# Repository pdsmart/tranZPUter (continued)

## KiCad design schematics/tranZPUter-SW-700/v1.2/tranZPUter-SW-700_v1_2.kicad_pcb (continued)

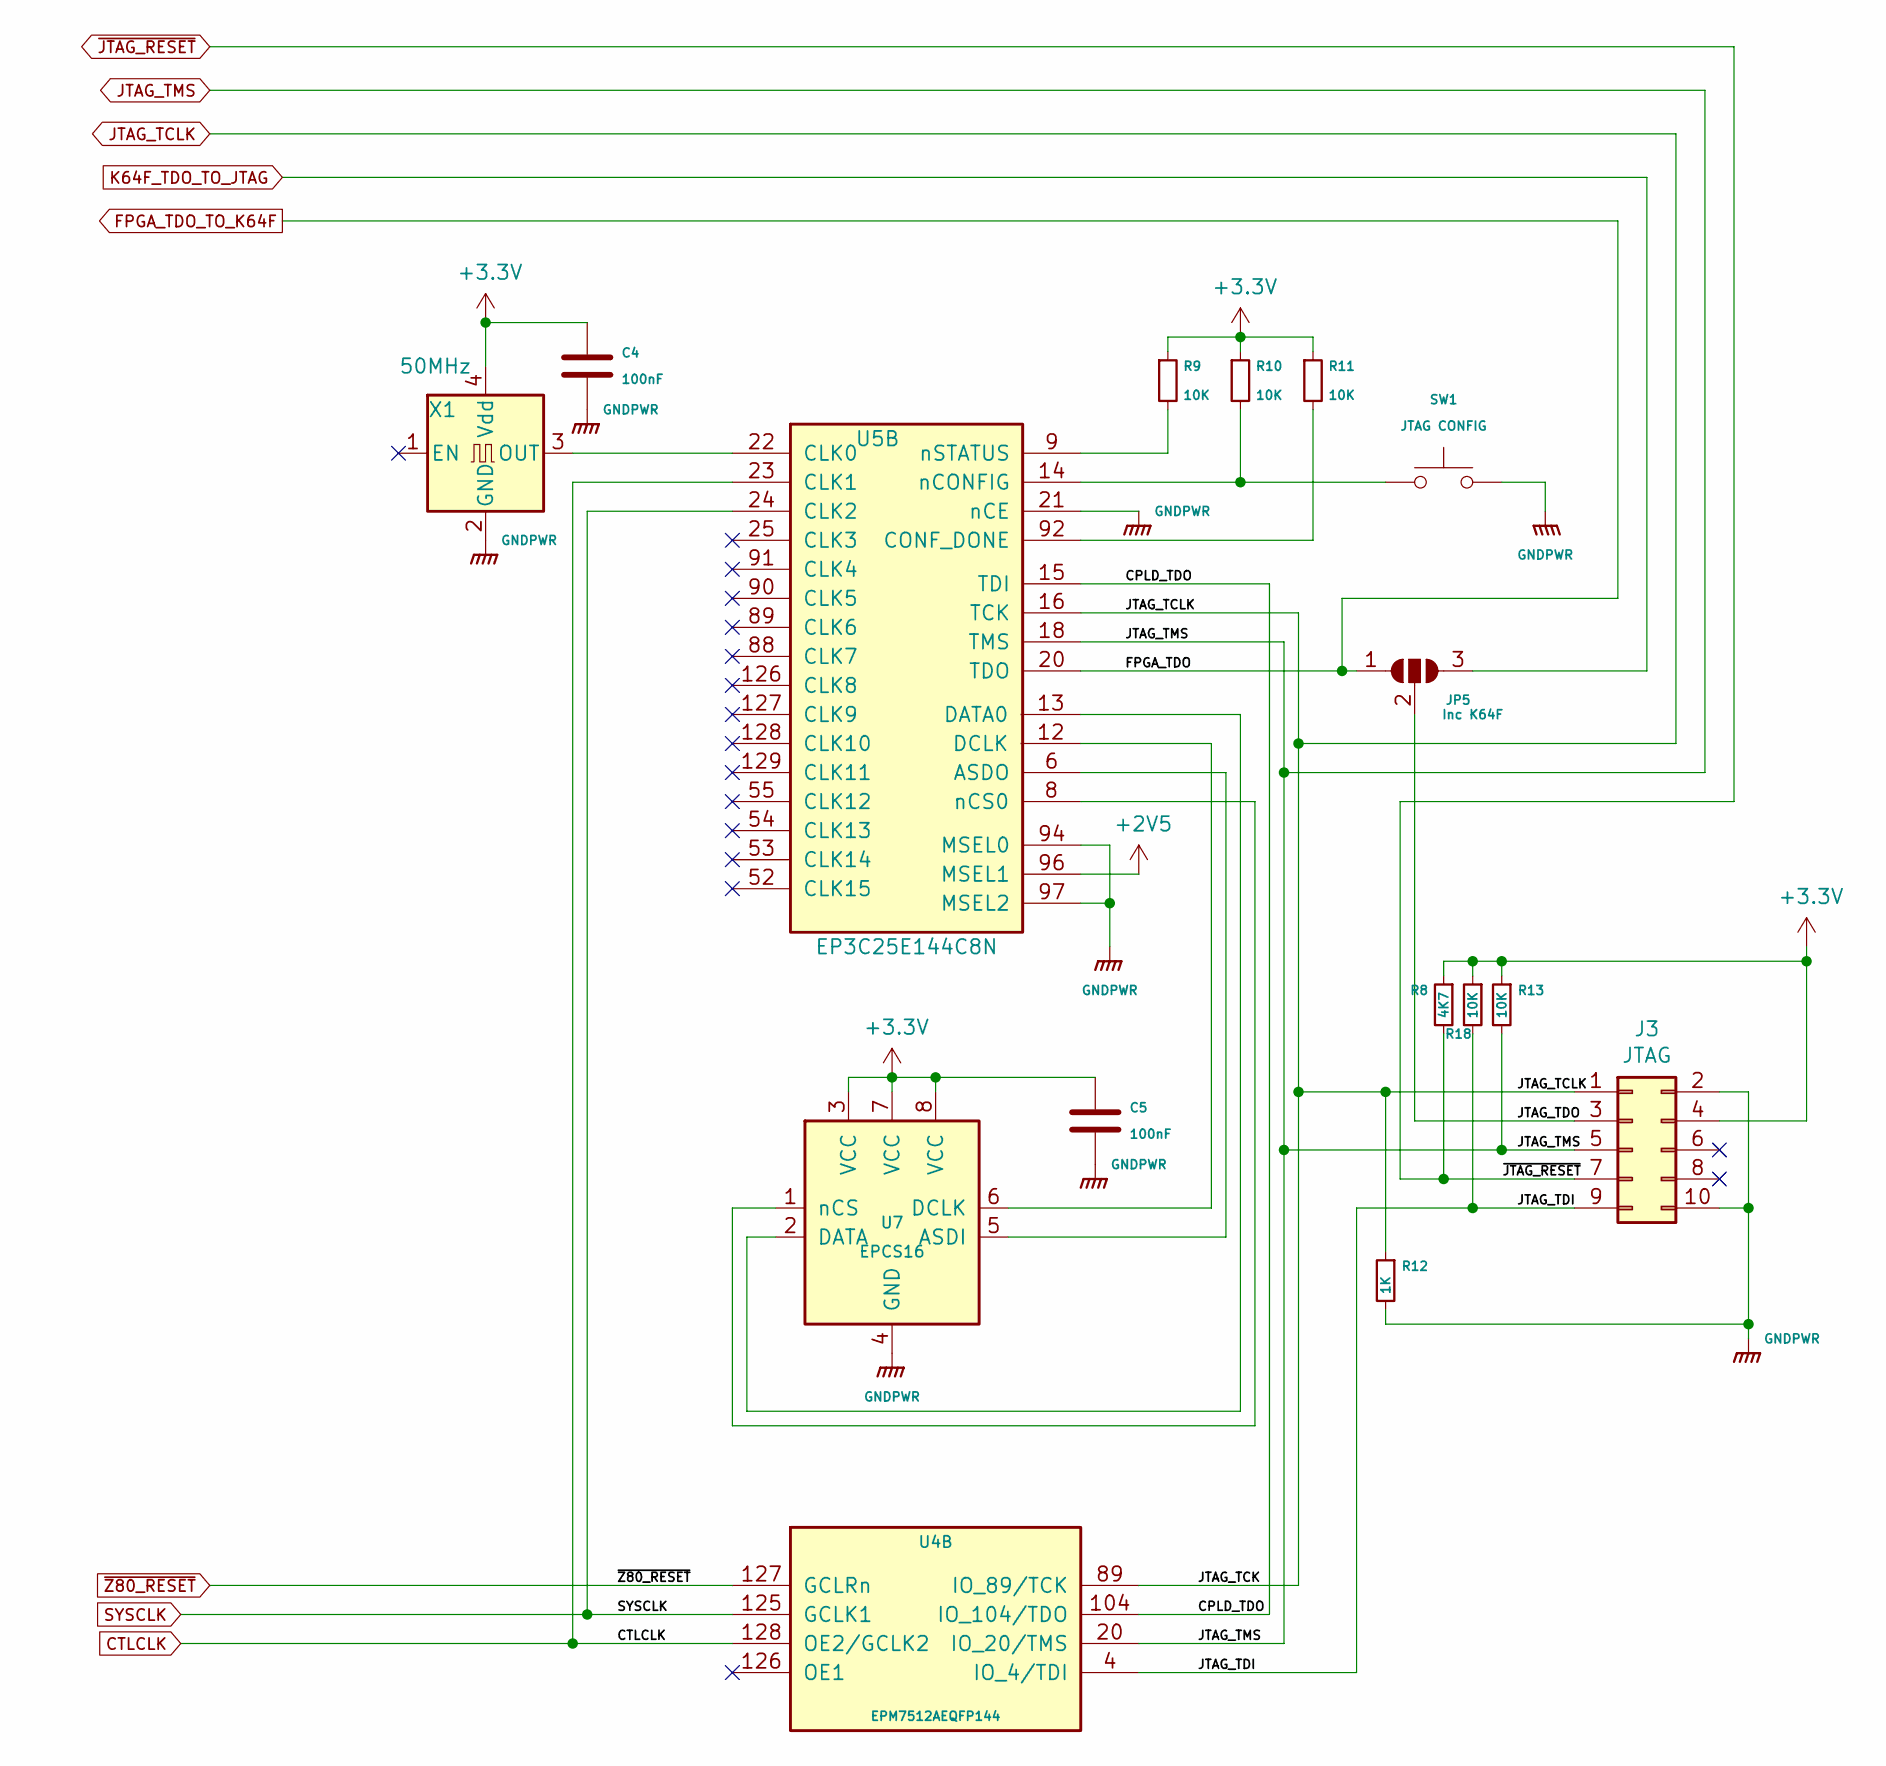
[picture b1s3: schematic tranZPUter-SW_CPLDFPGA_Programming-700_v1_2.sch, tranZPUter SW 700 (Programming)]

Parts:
C4, C5: 100nF; C_0603_1608Metric_Pad1.05x0.95mm_HandSolder
J3: JTAG; PinHeader_2x05_P2.54mm_Horizontal_NoBug
JP5: Inc K64F; SolderJumper-3_Open
R8: 4K7; R_0805_2012Metric_Pad1.15x1.40mm_HandSolder
R9, R10, R11, R13, R18: 10K; R_0805_2012Metric_Pad1.15x1.40mm_HandSolder
R12: 1K; R_0805_2012Metric_Pad1.15x1.40mm_HandSolder
SW1: JTAG CONFIG; SW_SPST_B3S-1000
U4: EPM7512AEQFP144; TQFP-144_20x20mm_P0.5mm
U5: EP3C25E144C8N; EQFP-144-1EP_20x20mm_P0.5mm_EP6.61x5.615mm
U7: EPCS16; SOIC-8_3.9x4.9mm_P1.27mm
X1: 50MHz; Oscillator_SMD_Abracon_ASE-4Pin_3.2x2.5mm

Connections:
+2V5: U5.96 (MSEL1); also elsewhere on the board
/CPLD and FPGA Programming/CPLD_TDO: U4.104 (IO_104/TDO), U5.15 (TDI)
/CPLD and FPGA Programming/JTAG_TDI: J3.9, R18.2, U4.4 (IO_4/TDI)
/CPLD and FPGA Programming/JTAG_TDO: J3.3, JP5.2 (C)
CTLCLK: U4.128 (OE2/GCLK2), U5.23 (CLK1); also elsewhere on the board
FPGA_TDO_TO_K64F: JP5.1 (A), U5.20 (TDO); also elsewhere on the board
GNDPWR: C4.2, C5.2, J3.2, J3.10, R12.2, SW1.2, U5.21 (nCE), U5.94 (MSEL0), U5.97 (MSEL2), U7.4 (GND), X1.2 (GND); also elsewhere on the board
JTAG_TCLK: J3.1, R12.1, U4.89 (IO_89/TCK), U5.16 (TCK); also elsewhere on the board
JTAG_TMS: J3.5, R13.2, U4.20 (IO_20/TMS), U5.18 (TMS); also elsewhere on the board
K64F_TDO_TO_JTAG: JP5.3 (B); also elsewhere on the board
unnamed: R9.2, U5.9 (nSTATUS)
unnamed: R10.2, SW1.1, U5.14 (nCONFIG)
unnamed: R11.2, U5.92 (CONF_DONE)
unnamed: U5.6 (ASDO), U7.5 (ASDI)
unnamed: U5.8 (nCS0), U7.1 (nCS)
unnamed: U5.12 (DCLK), U7.6 (DCLK)
unnamed: U5.13 (DATA0), U7.2 (DATA)
unnamed: U5.22 (CLK0), X1.3 (OUT)
SYSCLK: U4.125 (GCLK1), U5.24 (CLK2); also elsewhere on the board
~JTAG_RESET~: J3.7, R8.2; also elsewhere on the board
~Z80_RESET~: U4.127 (GCLRn); also elsewhere on the board

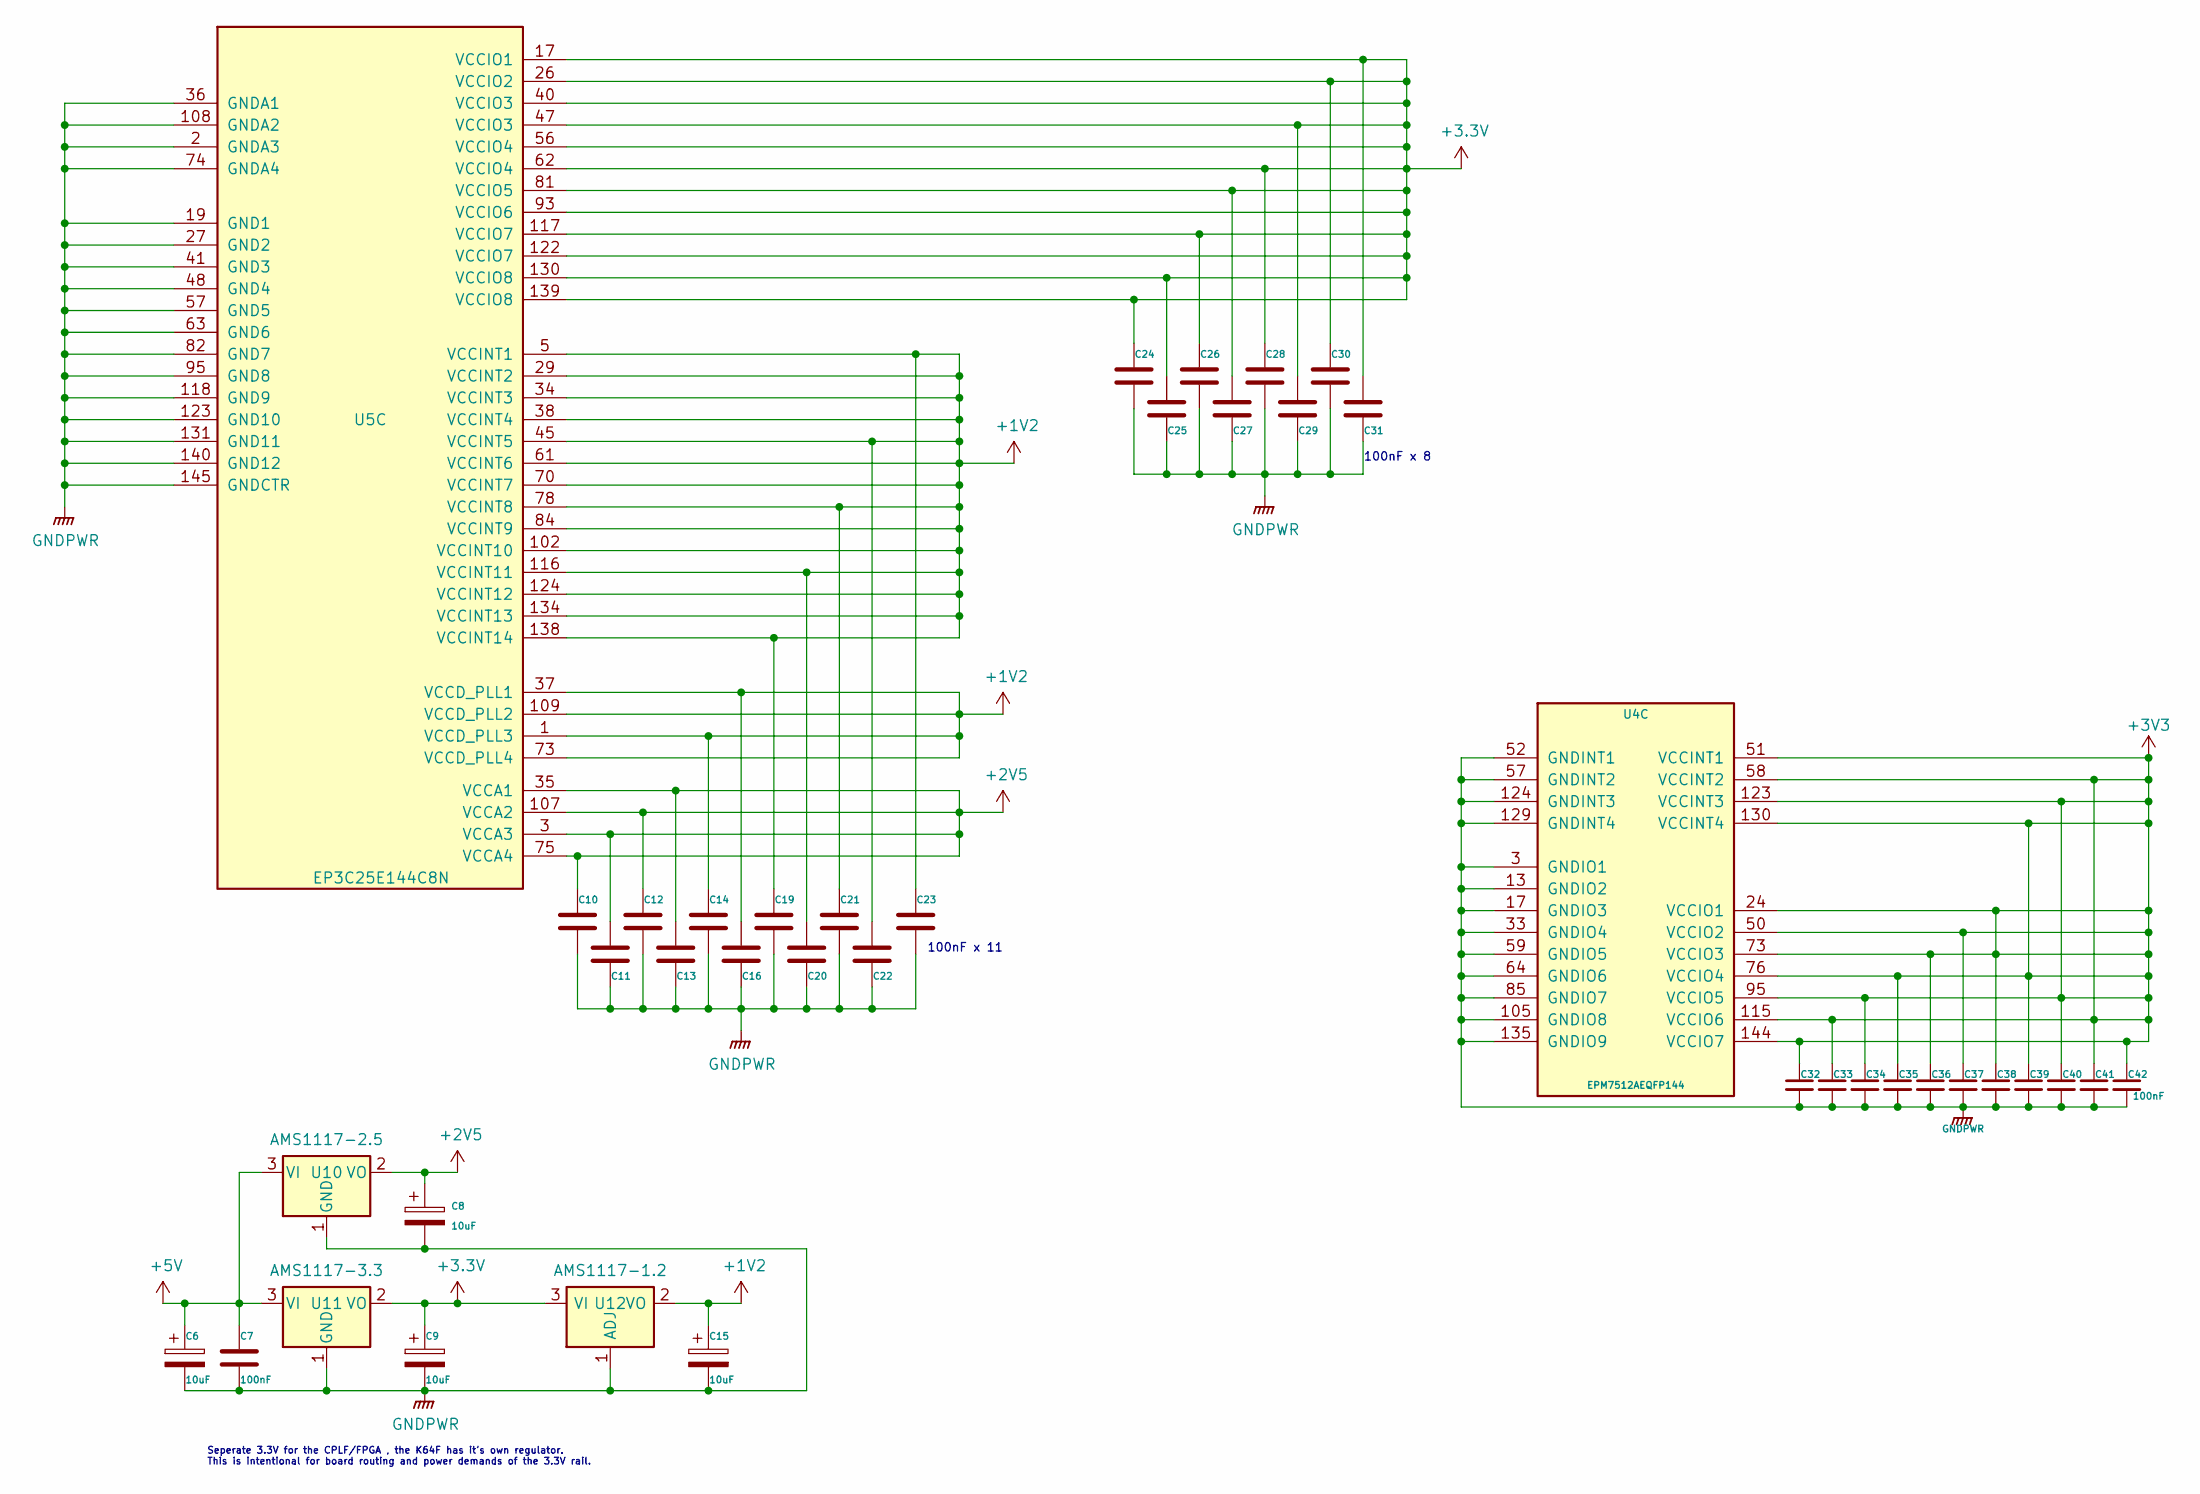
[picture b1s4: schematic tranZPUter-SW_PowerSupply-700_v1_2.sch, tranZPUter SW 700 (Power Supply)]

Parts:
C6, C8, C9, C15: 10uF; C_0603_1608Metric_Pad1.05x0.95mm_HandSolder
C7, C10, C11, C12, C13, C14, C16, C19, C20, C21, C22, C23, C27: 100nF; C_0603_1608Metric_Pad1.05x0.95mm_HandSolder
C24, C25, C26, C28, C29, C30, C31: 100nF; C_0805_2012Metric
C32, C33, C34, C35, C36, C37, C38, C39, C40, C41, C42: 100nF; C_0603_1608Metric
U4: EPM7512AEQFP144; TQFP-144_20x20mm_P0.5mm
U5: EP3C25E144C8N; EQFP-144-1EP_20x20mm_P0.5mm_EP6.61x5.615mm
U10: AMS1117-2.5; SOT-223-3_TabPin2
U11: AMS1117-3.3; SOT-223-3_TabPin2
U12: AMS1117-1.2; SOT-223-3_TabPin2

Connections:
+1V2: C14.1, C15.1, C16.1, C19.1, C20.1, C21.1, C22.1, C23.1, U5.1 (VCCD_PLL3), U5.5 (VCCINT1), U5.29 (VCCINT2), U5.34 (VCCINT3), U5.37 (VCCD_PLL1), U5.38 (VCCINT4), U5.45 (VCCINT5), U5.61 (VCCINT6), U5.70 (VCCINT7), U5.73 (VCCD_PLL4), U5.78 (VCCINT8), U5.84 (VCCINT9), U5.102 (VCCINT10), U5.109 (VCCD_PLL2), U5.116 (VCCINT11), U5.124 (VCCINT12), U5.134 (VCCINT13), U5.138 (VCCINT14), U12.2 (VO)
+2V5: C8.1, C10.1, C11.1, C12.1, C13.1, U5.3 (VCCA3), U5.35 (VCCA1), U5.75 (VCCA4), U5.107 (VCCA2), U10.2 (VO); also elsewhere on the board
+5V: C6.1, C7.1, U10.3 (VI), U11.3 (VI); also elsewhere on the board
GNDPWR: C6.2, C7.2, C8.2, C9.2, C10.2, C11.2, C12.2, C13.2, C14.2, C15.2, C16.2, C19.2, C20.2, C21.2, C22.2, C23.2, C24.2, C25.2, C26.2, C27.2, C28.2, C29.2, C30.2, C31.2, C32.2, C33.2, C34.2, C35.2, C36.2, C37.2, C38.2, C39.2, C40.2, C41.2, C42.2, U4.3 (GNDIO1), U4.13 (GNDIO2), U4.17 (GNDIO3), U4.33 (GNDIO4), U4.52 (GNDINT1), U4.57 (GNDINT2), U4.59 (GNDIO5), U4.64 (GNDIO6), U4.85 (GNDIO7), U4.105 (GNDIO8), U4.124 (GNDINT3), U4.129 (GNDINT4), U4.135 (GNDIO9), U5.2 (GNDA3), U5.19 (GND1), U5.27 (GND2), U5.36 (GNDA1), U5.41 (GND3), U5.48 (GND4), U5.57 (GND5), U5.63 (GND6), U5.74 (GNDA4), U5.82 (GND7), U5.95 (GND8), U5.108 (GNDA2), U5.118 (GND9), U5.123 (GND10), U5.131 (GND11), U5.140 (GND12), U5.145 (GNDCTR), U10.1 (GND), U11.1 (GND), U12.1 (ADJ); also elsewhere on the board

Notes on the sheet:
100nF x 11
100nF x 8
Seperate 3.3V for the CPLF/FPGA , the K64F has it’s own regulator. This is intentional for board routing and power demands of the 3.3V rail.

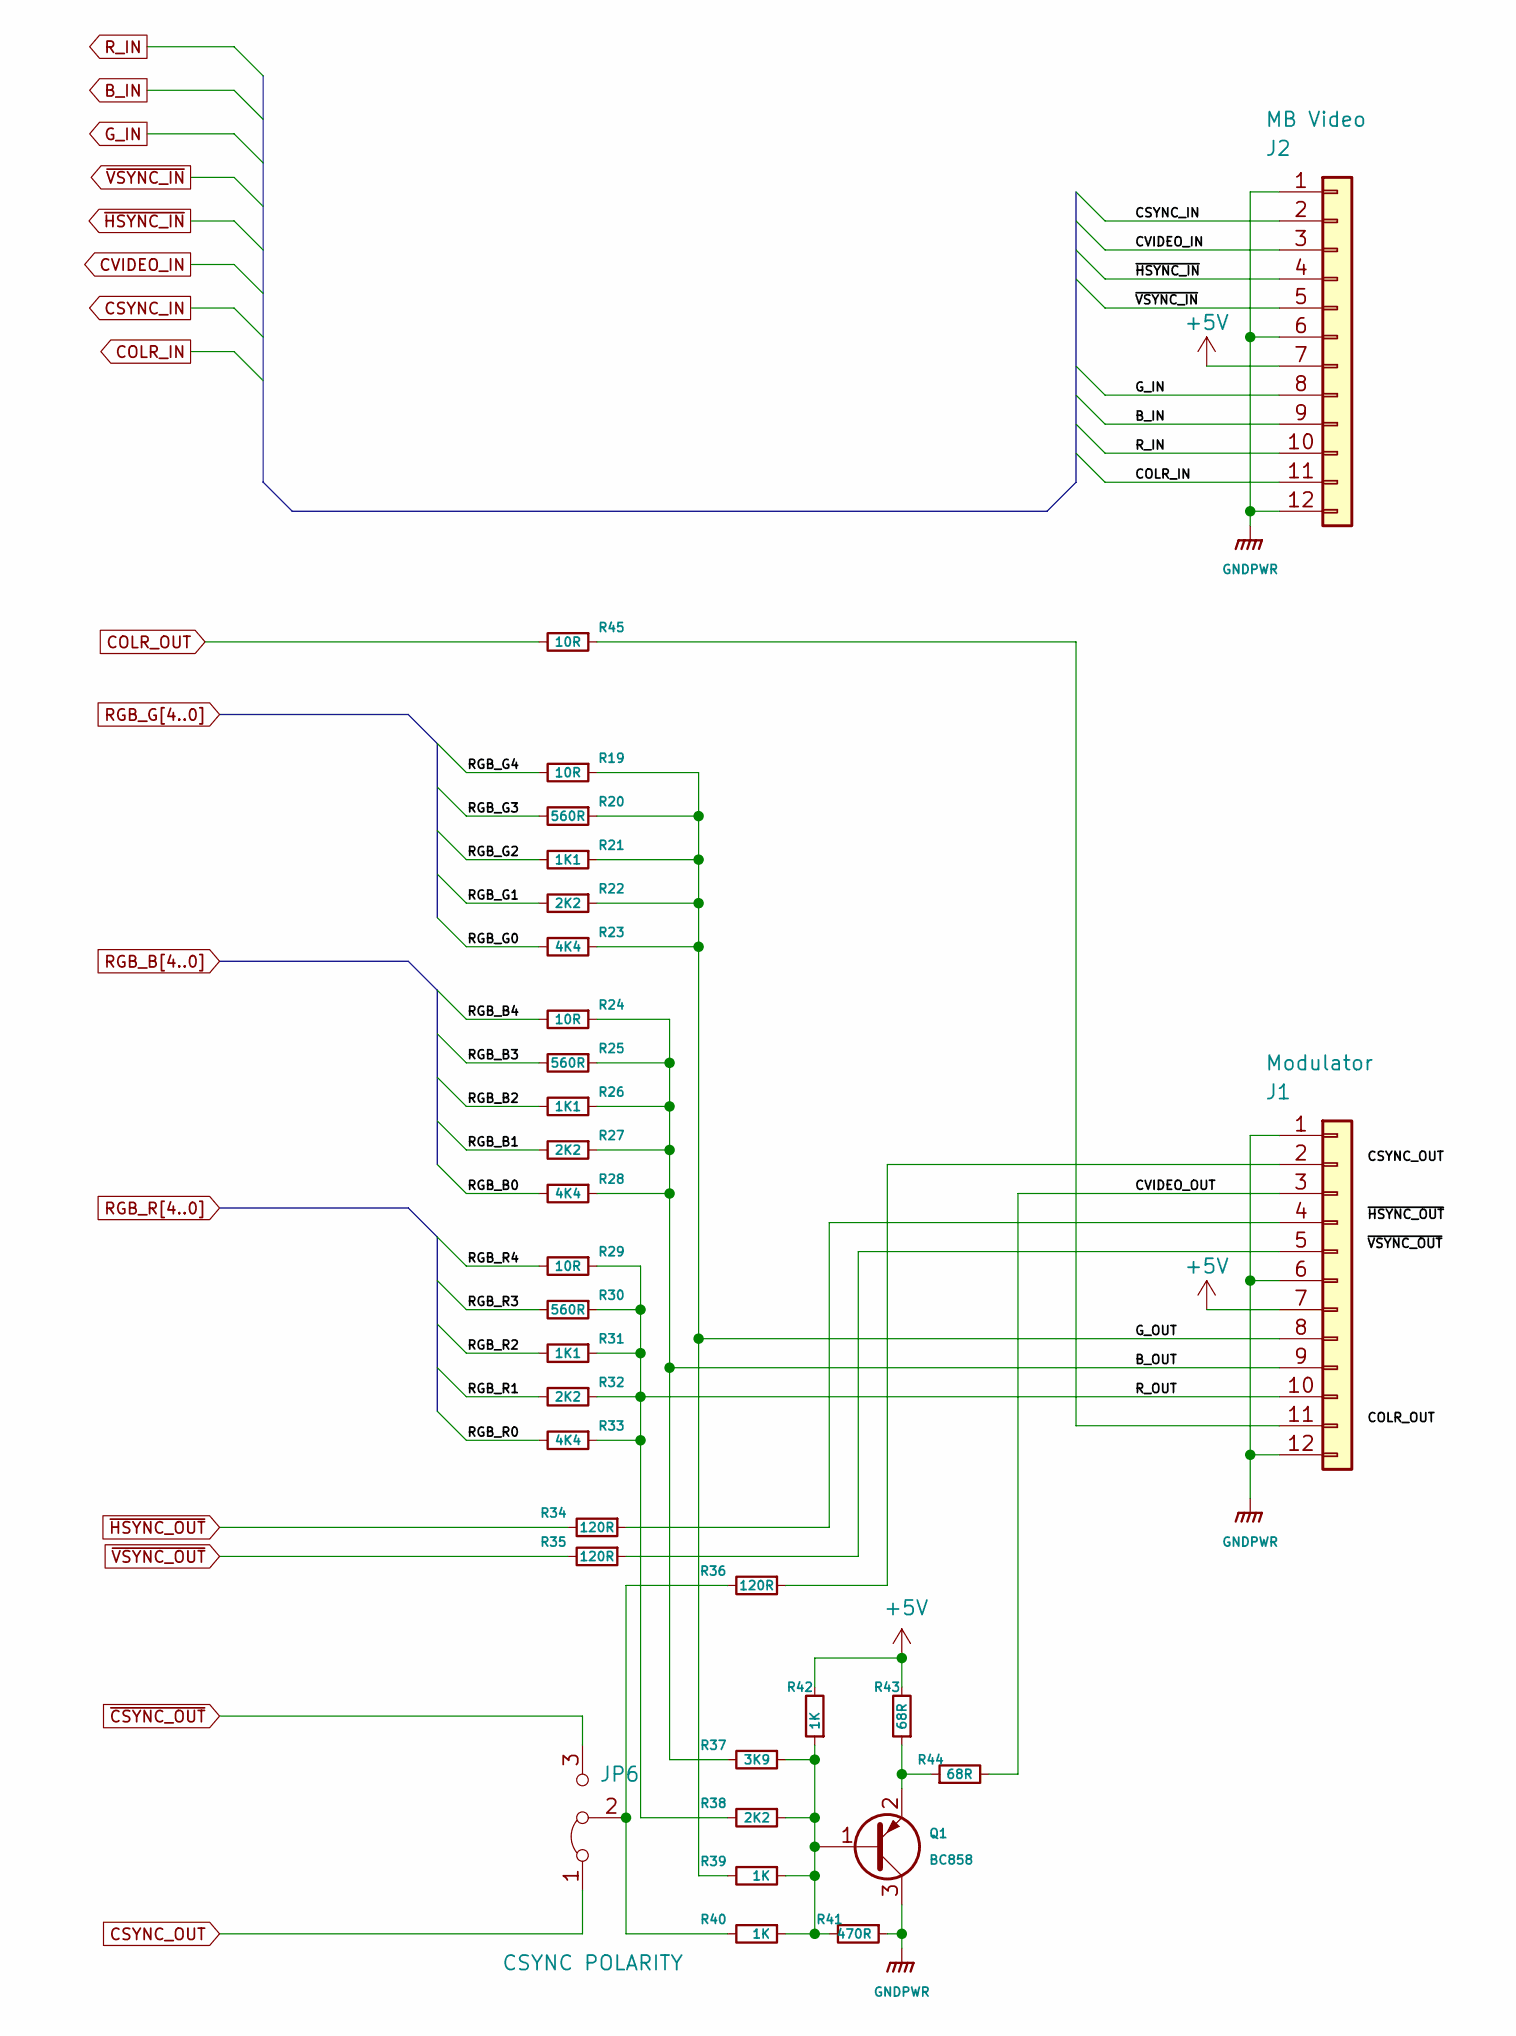
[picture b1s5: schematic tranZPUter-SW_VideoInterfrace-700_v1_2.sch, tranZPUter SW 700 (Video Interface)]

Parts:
J1: Modulator; PinHeader_1x12_P2.54mm_Vertical
J2: MB Video; PinHeader_1x12_P2.54mm_Vertical
JP6: CSYNC POLARITY; PinHeader_1x03_P2.00mm_Vertical
Q1: BC858; SOT-23
R19, R24, R29, R45: 10R; R_0805_2012Metric_Pad1.15x1.40mm_HandSolder
R20, R25, R30: 560R; R_0805_2012Metric_Pad1.15x1.40mm_HandSolder
R21, R26, R31: 1K1; R_0805_2012Metric_Pad1.15x1.40mm_HandSolder
R22, R27, R32, R38: 2K2; R_0805_2012Metric_Pad1.15x1.40mm_HandSolder
R23, R28, R33: 4K4; R_0805_2012Metric_Pad1.15x1.40mm_HandSolder
R34, R35, R36: 120R; R_0805_2012Metric_Pad1.15x1.40mm_HandSolder
R37: 3K9; R_0805_2012Metric_Pad1.15x1.40mm_HandSolder
R39, R40, R42: 1K; R_0805_2012Metric_Pad1.15x1.40mm_HandSolder
R41: 470R; R_0805_2012Metric_Pad1.15x1.40mm_HandSolder
R43, R44: 68R; R_0805_2012Metric_Pad1.15x1.40mm_HandSolder

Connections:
+5V: J1.7, J2.7, R42.2, R43.2; also elsewhere on the board
/Video Interface/B_OUT: J1.9, R24.1, R25.1, R26.1, R27.1, R28.1, R37.2
/Video Interface/CVIDEO_OUT: J1.3, R44.2
/Video Interface/G_OUT: J1.8, R19.1, R20.1, R21.1, R22.1, R23.1, R39.2
/Video Interface/R_OUT: J1.10, R29.1, R30.1, R31.1, R32.1, R33.1, R38.2
B_IN: J2.9; also elsewhere on the board
COLR_IN: J2.11; also elsewhere on the board
COLR_OUT: R45.2; also elsewhere on the board
CSYNC_IN: J2.2; also elsewhere on the board
CSYNC_OUT: JP6.1 (A); also elsewhere on the board
CVIDEO_IN: J2.3; also elsewhere on the board
GNDPWR: J1.1, J1.6, J1.12, J2.1, J2.6, J2.12, Q1.3 (C), R41.1; also elsewhere on the board
G_IN: J2.8; also elsewhere on the board
unnamed: J1.2, R36.1
unnamed: J1.4, R34.1
unnamed: J1.5, R35.1
unnamed: J1.11, R45.1
unnamed: JP6.2 (C), R36.2, R40.2
unnamed: Q1.1 (B), R37.1, R38.1, R39.1, R40.1, R41.2, R42.1
unnamed: Q1.2 (E), R43.1, R44.1
RGB_B0: R28.2; also elsewhere on the board
RGB_B1: R27.2; also elsewhere on the board
RGB_B2: R26.2; also elsewhere on the board
RGB_B3: R25.2; also elsewhere on the board
RGB_B4: R24.2; also elsewhere on the board
RGB_G0: R23.2; also elsewhere on the board
RGB_G1: R22.2; also elsewhere on the board
RGB_G2: R21.2; also elsewhere on the board
RGB_G3: R20.2; also elsewhere on the board
RGB_G4: R19.2; also elsewhere on the board
RGB_R0: R33.2; also elsewhere on the board
RGB_R1: R32.2; also elsewhere on the board
RGB_R2: R31.2; also elsewhere on the board
RGB_R3: R30.2; also elsewhere on the board
RGB_R4: R29.2; also elsewhere on the board
R_IN: J2.10; also elsewhere on the board
~CSYNC_OUT~: JP6.3 (B); also elsewhere on the board
~HSYNC_IN~: J2.4; also elsewhere on the board
~HSYNC_OUT~: R34.2; also elsewhere on the board
~VSYNC_IN~: J2.5; also elsewhere on the board
~VSYNC_OUT~: R35.2; also elsewhere on the board

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
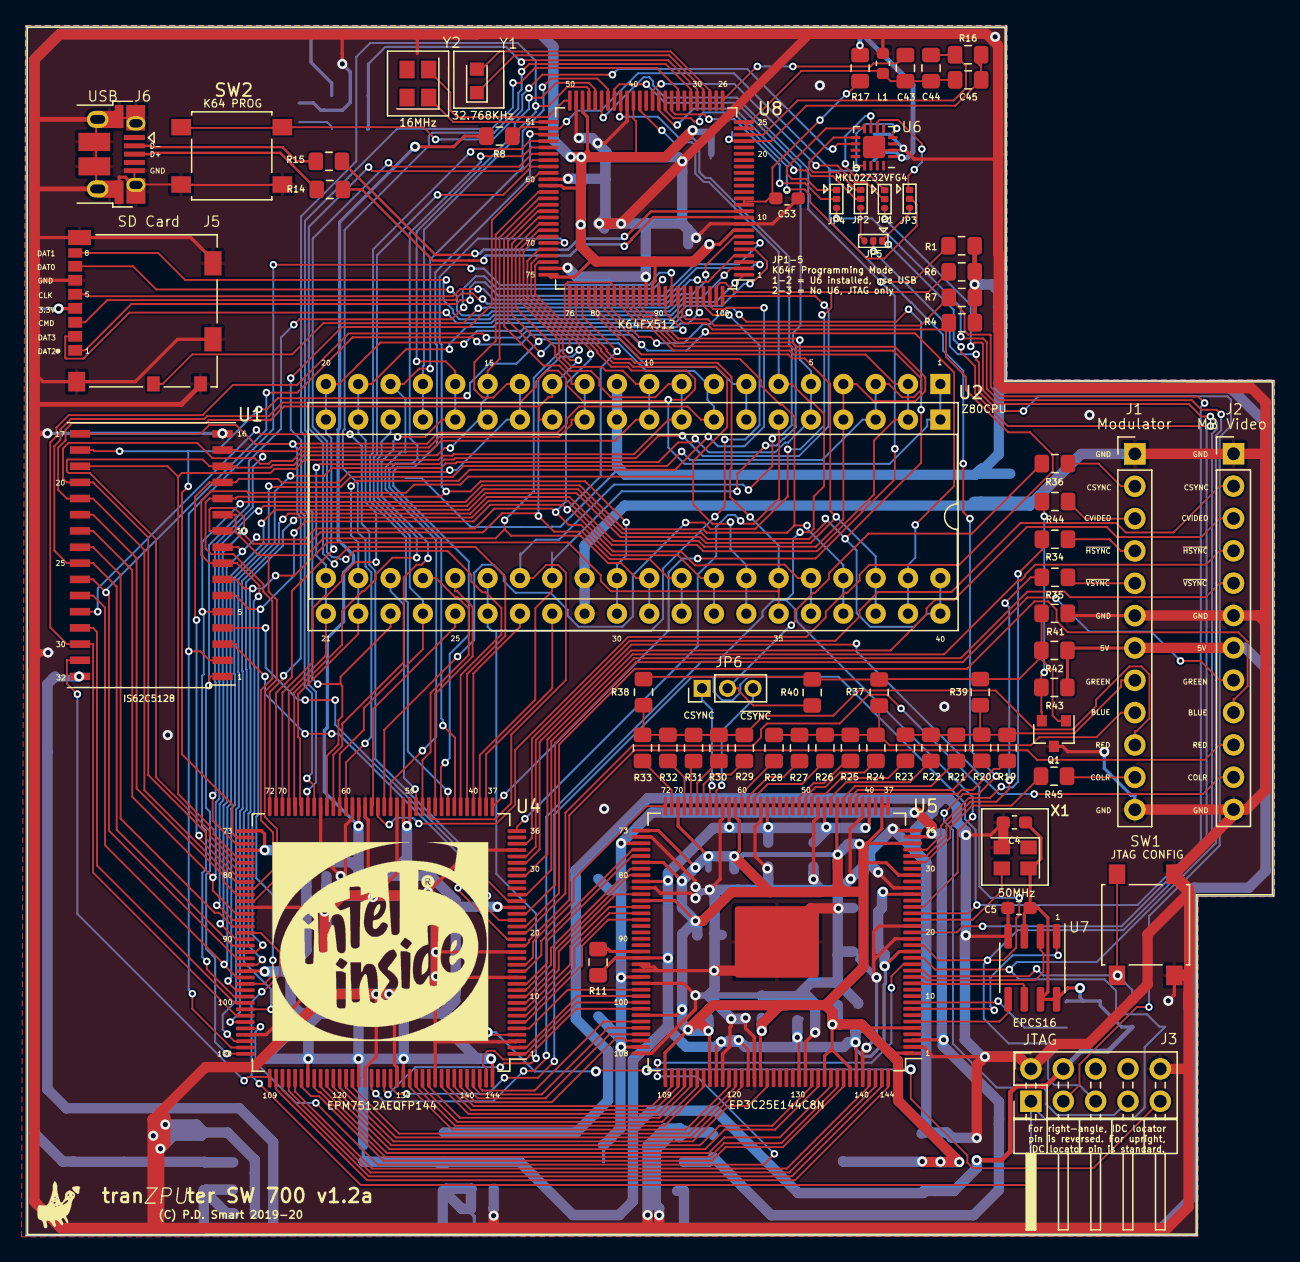
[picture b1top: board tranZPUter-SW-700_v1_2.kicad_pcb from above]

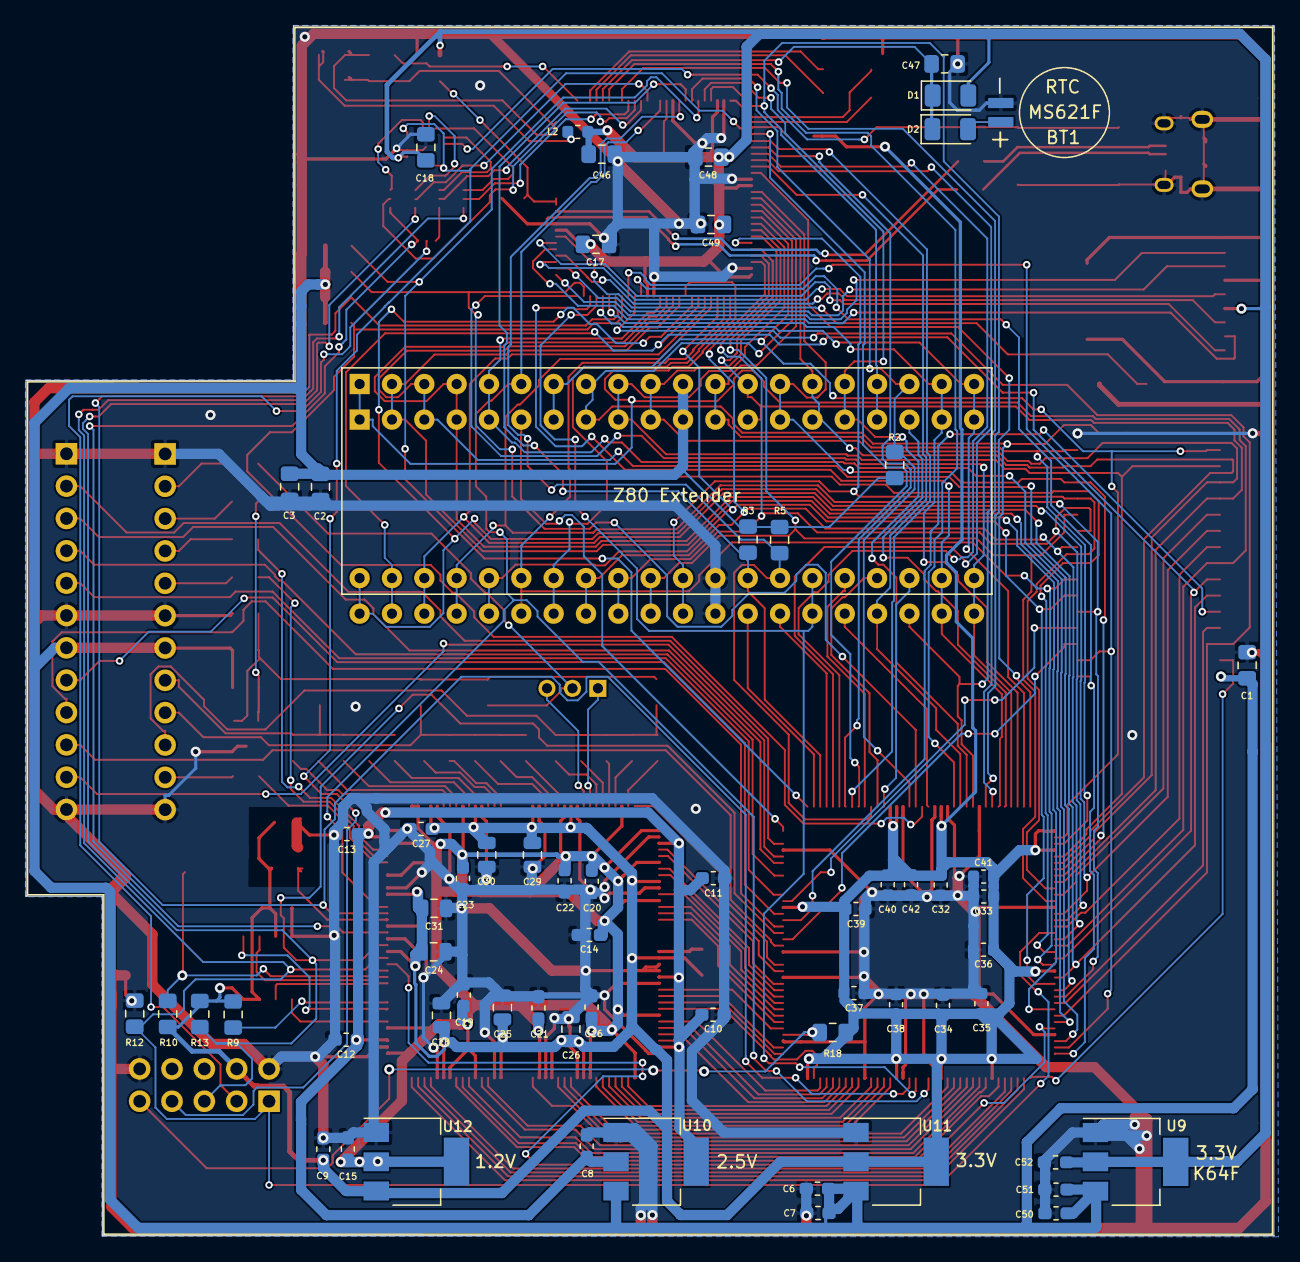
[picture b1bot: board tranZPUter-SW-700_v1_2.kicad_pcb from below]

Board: 2 copper layers, 98.0 x 95.0 mm, 132 parts (63 on the bottom side), 194 nets.

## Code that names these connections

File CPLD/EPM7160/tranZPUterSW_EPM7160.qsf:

# -------------------------------------------------------------------------- #
#
# Copyright (C) 1991-2013 Altera Corporation
# Your use of Altera Corporation's design tools, logic functions 
# and other software and tools, and its AMPP partner logic 
# functions, and any output files from any of the foregoing 
# (including device programming or simulation files), and any 
# associated documentation or information are expressly subject 
# to the terms and conditions of the Altera Program License 
# Subscription Agreement, Altera MegaCore Function License 
# Agreement, or other applicable license agreement, including, 
# without limitation, that your use is for the sole purpose of 
# programming logic devices manufactured by Altera and sold by 
# Altera or its authorized distributors.  Please refer to the 
# applicable agreement for further details.
#
# -------------------------------------------------------------------------- #
#
# Quartus II 64-Bit
# Version 13.0.1 Build 232 06/12/2013 Service Pack 1 SJ Web Edition
# Date created = 16:29:32  June 24, 2020
#
# -------------------------------------------------------------------------- #
#
# Notes:
#
# 1) The default values for assignments are stored in the file:
#		tranZPUterSW_assignment_defaults.qdf
#    If this file doesn't exist, see file:
#		assignment_defaults.qdf
#
# 2) Altera recommends that you do not modify this file. This
#    file is updated automatically by the Quartus II software
#    and any changes you make may be lost or overwritten.
#
# -------------------------------------------------------------------------- #


set_global_assignment -name FAMILY MAX7000S
set_global_assignment -name DEVICE "EPM7160STC100-10"
set_global_assignment -name TOP_LEVEL_ENTITY tranZPUterSW
set_global_assignment -name ORIGINAL_QUARTUS_VERSION "13.0 SP1"
set_global_assignment -name PROJECT_CREATION_TIME_DATE "16:29:32  JUNE 24, 2020"
set_global_assignment -name LAST_QUARTUS_VERSION "13.0 SP1"
set_global_assignment -name PROJECT_OUTPUT_DIRECTORY output_files
set_global_assignment -name ERROR_CHECK_FREQUENCY_DIVISOR "-1"
set_global_assignment -name EDA_DESIGN_ENTRY_SYNTHESIS_TOOL "<None>"
set_global_assignment -name EDA_INPUT_VCC_NAME VDD -section_id eda_design_synthesis
set_global_assignment -name EDA_INPUT_DATA_FORMAT EDIF -section_id eda_design_synthesis
set_global_assignment -name EDA_SIMULATION_TOOL "ModelSim-Altera (VHDL)"
set_global_assignment -name EDA_OUTPUT_DATA_FORMAT VHDL -section_id eda_simulation
set_global_assignment -name OPTIMIZE_HOLD_TIMING OFF
set_global_assignment -name OPTIMIZE_MULTI_CORNER_TIMING OFF
set_global_assignment -name FITTER_EFFORT "STANDARD FIT"
set_global_assignment -name MAX7000_DEVICE_IO_STANDARD TTL

# Z80 Address Bus
# ===============
set_location_assignment PIN_79 -to Z80_HI_ADDR[18]
set_location_assignment PIN_78 -to Z80_HI_ADDR[17]
set_location_assignment PIN_77 -to Z80_HI_ADDR[16]
set_location_assignment PIN_76 -to Z80_ADDR[15]
set_location_assignment PIN_75 -to Z80_ADDR[14]
set_location_assignment PIN_72 -to Z80_ADDR[13]
set_location_assignment PIN_71 -to Z80_ADDR[12]
set_location_assignment PIN_70 -to Z80_ADDR[11]
set_location_assignment PIN_69 -to Z80_ADDR[10]
set_location_assignment PIN_68 -to Z80_ADDR[9]
set_location_assignment PIN_67 -to Z80_ADDR[8]
set_location_assignment PIN_65 -to Z80_ADDR[7]
set_location_assignment PIN_64 -to Z80_ADDR[6]
set_location_assignment PIN_63 -to Z80_ADDR[5]
set_location_assignment PIN_61 -to Z80_ADDR[4]
set_location_assignment PIN_60 -to Z80_ADDR[3]
set_location_assignment PIN_58 -to Z80_ADDR[2]
set_location_assignment PIN_57 -to Z80_ADDR[1]
set_location_assignment PIN_56 -to Z80_ADDR[0]

# Z80 Data Bus
# ============
set_location_assignment PIN_55 -to Z80_DATA[0]
set_location_assignment PIN_54 -to Z80_DATA[1]
set_location_assignment PIN_53 -to Z80_DATA[2]
set_location_assignment PIN_52 -to Z80_DATA[3]
set_location_assignment PIN_50 -to Z80_DATA[4]
set_location_assignment PIN_49 -to Z80_DATA[5]
set_location_assignment PIN_48 -to Z80_DATA[6]
set_location_assignment PIN_47 -to Z80_DATA[7]

# Graphics extension address and control.
# =======================================
set_location_assignment PIN_5 -to VADDR[13]
set_location_assignment PIN_6 -to VADDR[12]
set_location_assignment PIN_7 -to VADDR[11]
set_location_assignment PIN_1 -to VMEM_CSn

# RAM control
# ===========
set_location_assignment PIN_81 -to RAM_CSn
set_location_assignment PIN_16 -to RAM_OEn
set_location_assignment PIN_17 -to RAM_WEn

# K64F Interrupt requests
# =======================
set_location_assignment PIN_8 -to SYSREQn
set_location_assignment PIN_9 -to SVCREQn

# K64F control
# ============
set_location_assignment PIN_20 -to CTL_WAITn
set_location_assignment PIN_21 -to CTL_RFSHn
set_location_assignment PIN_19 -to CTL_CLKSLCT
set_location_assignment PIN_25 -to CTL_HALTn
set_location_assignment PIN_90 -to CTLCLK
set_location_assignment PIN_23 -to CTL_M1n
set_location_assignment PIN_24 -to CTL_BUSACKn
set_location_assignment PIN_22 -to CTL_BUSRQn
set_location_assignment PIN_42 -to TZ_BUSACKn
set_location_assignment PIN_94 -to ENIOWAIT
set_location_assignment PIN_96 -to Z80_MEM[4]
set_location_assignment PIN_97 -to Z80_MEM[3]
set_location_assignment PIN_98 -to Z80_MEM[2]
set_location_assignment PIN_99 -to Z80_MEM[1]
set_location_assignment PIN_100 -to Z80_MEM[0]
set_location_assignment PIN_84 -to TBA[0]
set_location_assignment PIN_85 -to TBA[1]
set_location_assignment PIN_92 -to TBA[2]
set_location_assignment PIN_93 -to TBA[3]

# Z80 Control signals.
# ====================
set_location_assignment PIN_36 -to Z80_MREQn
set_location_assignment PIN_35 -to Z80_IORQn
set_location_assignment PIN_33 -to Z80_RDn
set_location_assignment PIN_32 -to Z80_WRn
set_location_assignment PIN_31 -to Z80_RFSHn
set_location_assignment PIN_30 -to Z80_M1n
set_location_assignment PIN_29 -to Z80_WAITn
set_location_assignment PIN_44 -to Z80_HALTn
set_location_assignment PIN_28 -to Z80_BUSACKn
set_location_assignment PIN_27 -to Z80_BUSRQn
set_location_assignment PIN_40 -to Z80_INTn
set_location_assignment PIN_37 -to Z80_NMIn
set_location_assignment PIN_80 -to Z80_CLK
set_location_assignment PIN_89 -to Z80_RESETn

# Mainboard control signals.
# ==========================
set_location_assignment PIN_87 -to SYSCLK
set_location_assignment PIN_12 -to SYS_WAITn
set_location_assignment PIN_10 -to SYS_BUSRQn
set_location_assignment PIN_13 -to SYS_BUSACKn

set_global_assignment -name VHDL_FILE ../tranZPUterSW_Toplevel_EPM7160.vhd
set_global_assignment -name VHDL_FILE ../tranZPUterSW_pkg_EPM7160.vhd
set_global_assignment -name VHDL_FILE ../tranZPUterSW_EPM7160.vhd
set_global_assignment -name SDC_FILE tranZPUterSW_constraints_EPM7160.sdc

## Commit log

2019-10-25 First push
2019-10-25 Additional files
2019-10-25 Tidy
2019-10-26 Removed unneeded files
2019-11-11 Set theme jekyll-theme-tactile
2020-01-14 Updates to SDRAM and SoC
2020-02-28 Work in progress, not a stable build
2020-04-25 Migrated initial software away and merged into zOS repository
2020-04-28 Added READNE, schematic and Gerber files for tranZPUterSW
2020-05-18 Tool to create the memory decoder bit map
2020-05-19 Updates to README
2020-05-29 Initial developments of TZFS and preparation of CPM
2020-06-02 CPM dev
2020-06-03 More CPM updates
2020-06-03 Updated changed schematic
2020-06-08 Memory map changes for Sharp MZ700 mode
2020-06-10 Updates to test the MZ700 memory mode switching
2020-06-10 Frequency change and MZ700 mode additions
2020-06-10 Updated schematic
2020-06-17 Added Microsoft BASIC converted for Sharp and tranZPUter
2020-06-19 BASIC Command additions
2020-07-04 WIP tranZPUterSW v2
2020-07-04 Updated schematics
2020-07-12 Updated basic from changes made for RFS
2020-07-16 Updates for v1.1 board
2020-07-24 v2.1 first cut
2020-07-25 Updated the MZ700 keyboard logic
2020-07-25 Comment tweaks
2020-07-29 Updates for v2.1 board
2020-07-29 Updates for v2.1 of the tranZPUter board
2020-07-31 Changes to MZ-700 scanning to ensure tape drive works correctly
2020-09-02 Updates for v2.1 hardware. Will now create branches for v2.2 and v2.1 hardware
2020-09-02 New schematic for v2.2
2020-09-04 Correction
2020-09-05 Updates to for better Video Module connectivity
2020-09-05 Updated to build for the Video Module
2020-09-06 Updates to CPM and Microsoft BASIC to configure the new Video Module and system board speed
2020-09-08 Changes to the serialiser in order to get the pixel mapped graphics working - needs more changes as it isnt reliable at 4MHz mainboard frequency
2020-11-02 Video and tranZPUter developments for the SW700 board
2020-11-08 Updates for SW-700 board
2020-11-10 Bug fixes and tweaks
2020-11-14 Updates to video logic
2020-12-12 Split for v1.2 and v1.3 developments
2021-02-06 Latest updates adding soft processors
2021-02-06 Added schematics, kicad and pcb gerber files
2021-03-03 Removed files which shouldnt be on github
2021-03-03 Removed files which shouldnt be on git
2021-03-06 Bug fix and addition of batch tape to sd command
2021-03-07 Updates for the tranZPUter SW v2.2 on the MZ800
2021-03-26 Updates for MZ-700/800
2021-04-04 Updates and bug fixes
2021-04-18 sync with rfs, 40/80 versions, bug fixes
2021-04-25 Updates to MSBASIC and SA-5510 for use with SD card.
2021-05-08 Tranzputer updates and split of coreMZ in preparation for the SharpMZ Emulator being embedded
2021-05-09 Tidy up and remove old code
2021-05-11 Minor update to TZFS
2021-05-15 Minor tweaks
2021-05-15 Missing build.sh file added
2021-08-21 Updated ignore
